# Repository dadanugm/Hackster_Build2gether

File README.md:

# Hackster_Build2gether
Hackster_Build2gether contest repo

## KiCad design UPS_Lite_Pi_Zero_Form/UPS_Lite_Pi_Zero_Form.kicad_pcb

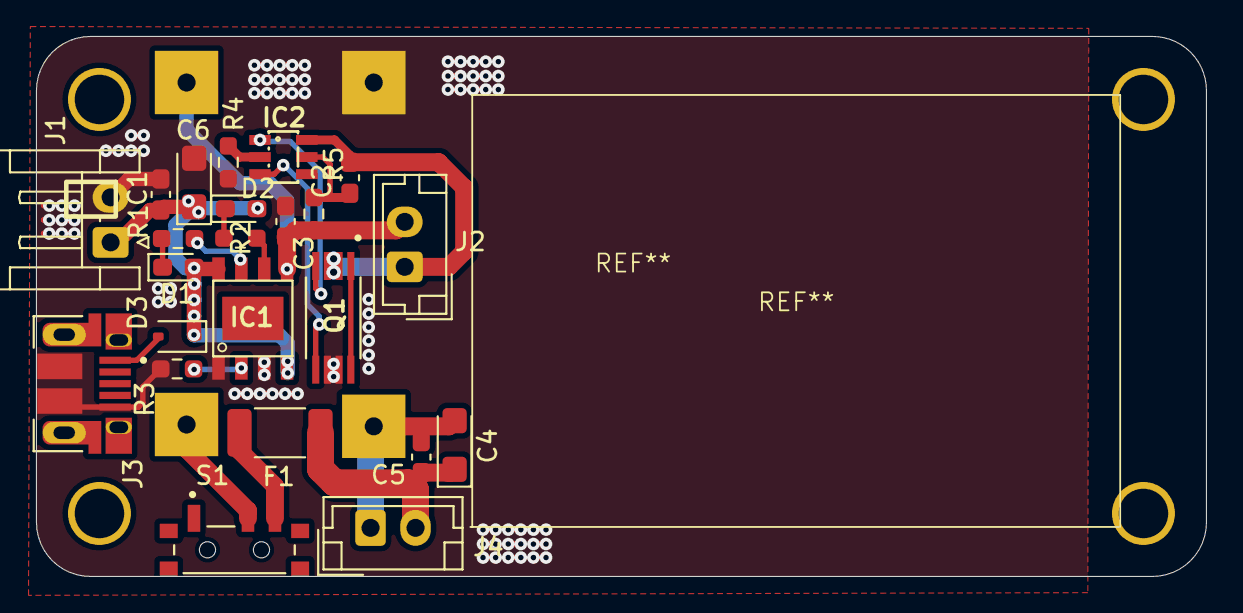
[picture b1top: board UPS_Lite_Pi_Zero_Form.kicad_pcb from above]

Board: 2 copper layers, 65.0 x 30.0 mm, 24 parts (1 on the bottom side), 19 nets.

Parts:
C1, C2: 100nf; C_0603_1608Metric_Pad1.08x0.95mm_HandSolder
C3, C5: 10uF; C_0603_1608Metric_Pad1.08x0.95mm_HandSolder
C4, C6: C_Polarized; CP_EIA-3216-18_Kemet-A
D1, D2: LED; LED_0603_1608Metric_Pad1.05x0.95mm_HandSolder
D3: 1N5819WS; D_SOD-323
F1: Polyfuse_Small; Fuse_2010_5025Metric
IC1: TP4056
IC2: DW01A
J1: Conn_01x02_Male; JST_EH_S2B-EH_1x02_P2.50mm_Horizontal
J2, J4: Conn_01x02_Male; JST_EH_B2B-EH-A_1x02_P2.50mm_Vertical
J3: Micro-USB1
Q1: FS8205A; FS8205
R1, R2, R4: 1K; R_0603_1608Metric_Pad0.98x0.95mm_HandSolder
R3: 1.2K; R_0603_1608Metric_Pad0.98x0.95mm_HandSolder
R5: 100; R_0603_1608Metric_Pad0.98x0.95mm_HandSolder
S1: EG1215AA; SW_Slide_SPST_Side
U*1: Boost_5V_3A

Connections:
/5V_3A: C4.1, C5.1, F1.2, J4.2
/BATT+: C3.1, IC1.5 (BAT), J2.2, R5.2, U*1.1 (IN+)
/BATT-: C2.2, IC2.6 (GND), J2.1, Q1.2, Q1.3
/BATT_SAVE: C2.1, IC2.5 (VCC), R5.1
/BATT_VIN: C1.1, C6.1, D1.2 (A), D2.2 (A), D3.1 (K), IC1.4 (VCC), IC1.8 (CE), J1.1
/CS: IC2.2 (CS), R4.1
/OC: IC2.3 (OC), Q1.5
/OD: IC2.1 (OD), Q1.4
GND: C1.2, C3.2, C6.2, IC1.1 (TEMP), IC1.3 (GND), J1.2, J3.5 (GND), J3.6 (SHIELD), J3.7 (SHIELD), J3.8 (SHIELD), J3.9 (SHIELD), J3.10 (SHIELD), J3.11 (SHIELD), J3.S1 (SHIELD), J3.S2 (SHIELD), Q1.6, Q1.7, R3.1, R4.2, U*1.2 (IN-)
unnamed: D1.1 (K), R1.2
unnamed: D2.1 (K), R2.2
unnamed: D3.2 (A), J3.1 (VCC)
unnamed: F1.1, S1.3
unnamed: IC1.7 (CHRG), R1.1
unnamed: IC1.2 (PROG), R3.2
unnamed: IC1.6 (STDBY), R2.1
unnamed: C4.2, C5.2, J4.1, U*1.4 (OUT-)
unnamed: Q1.1, Q1.8
unnamed: S1.2, U*1.3 (OUT+)

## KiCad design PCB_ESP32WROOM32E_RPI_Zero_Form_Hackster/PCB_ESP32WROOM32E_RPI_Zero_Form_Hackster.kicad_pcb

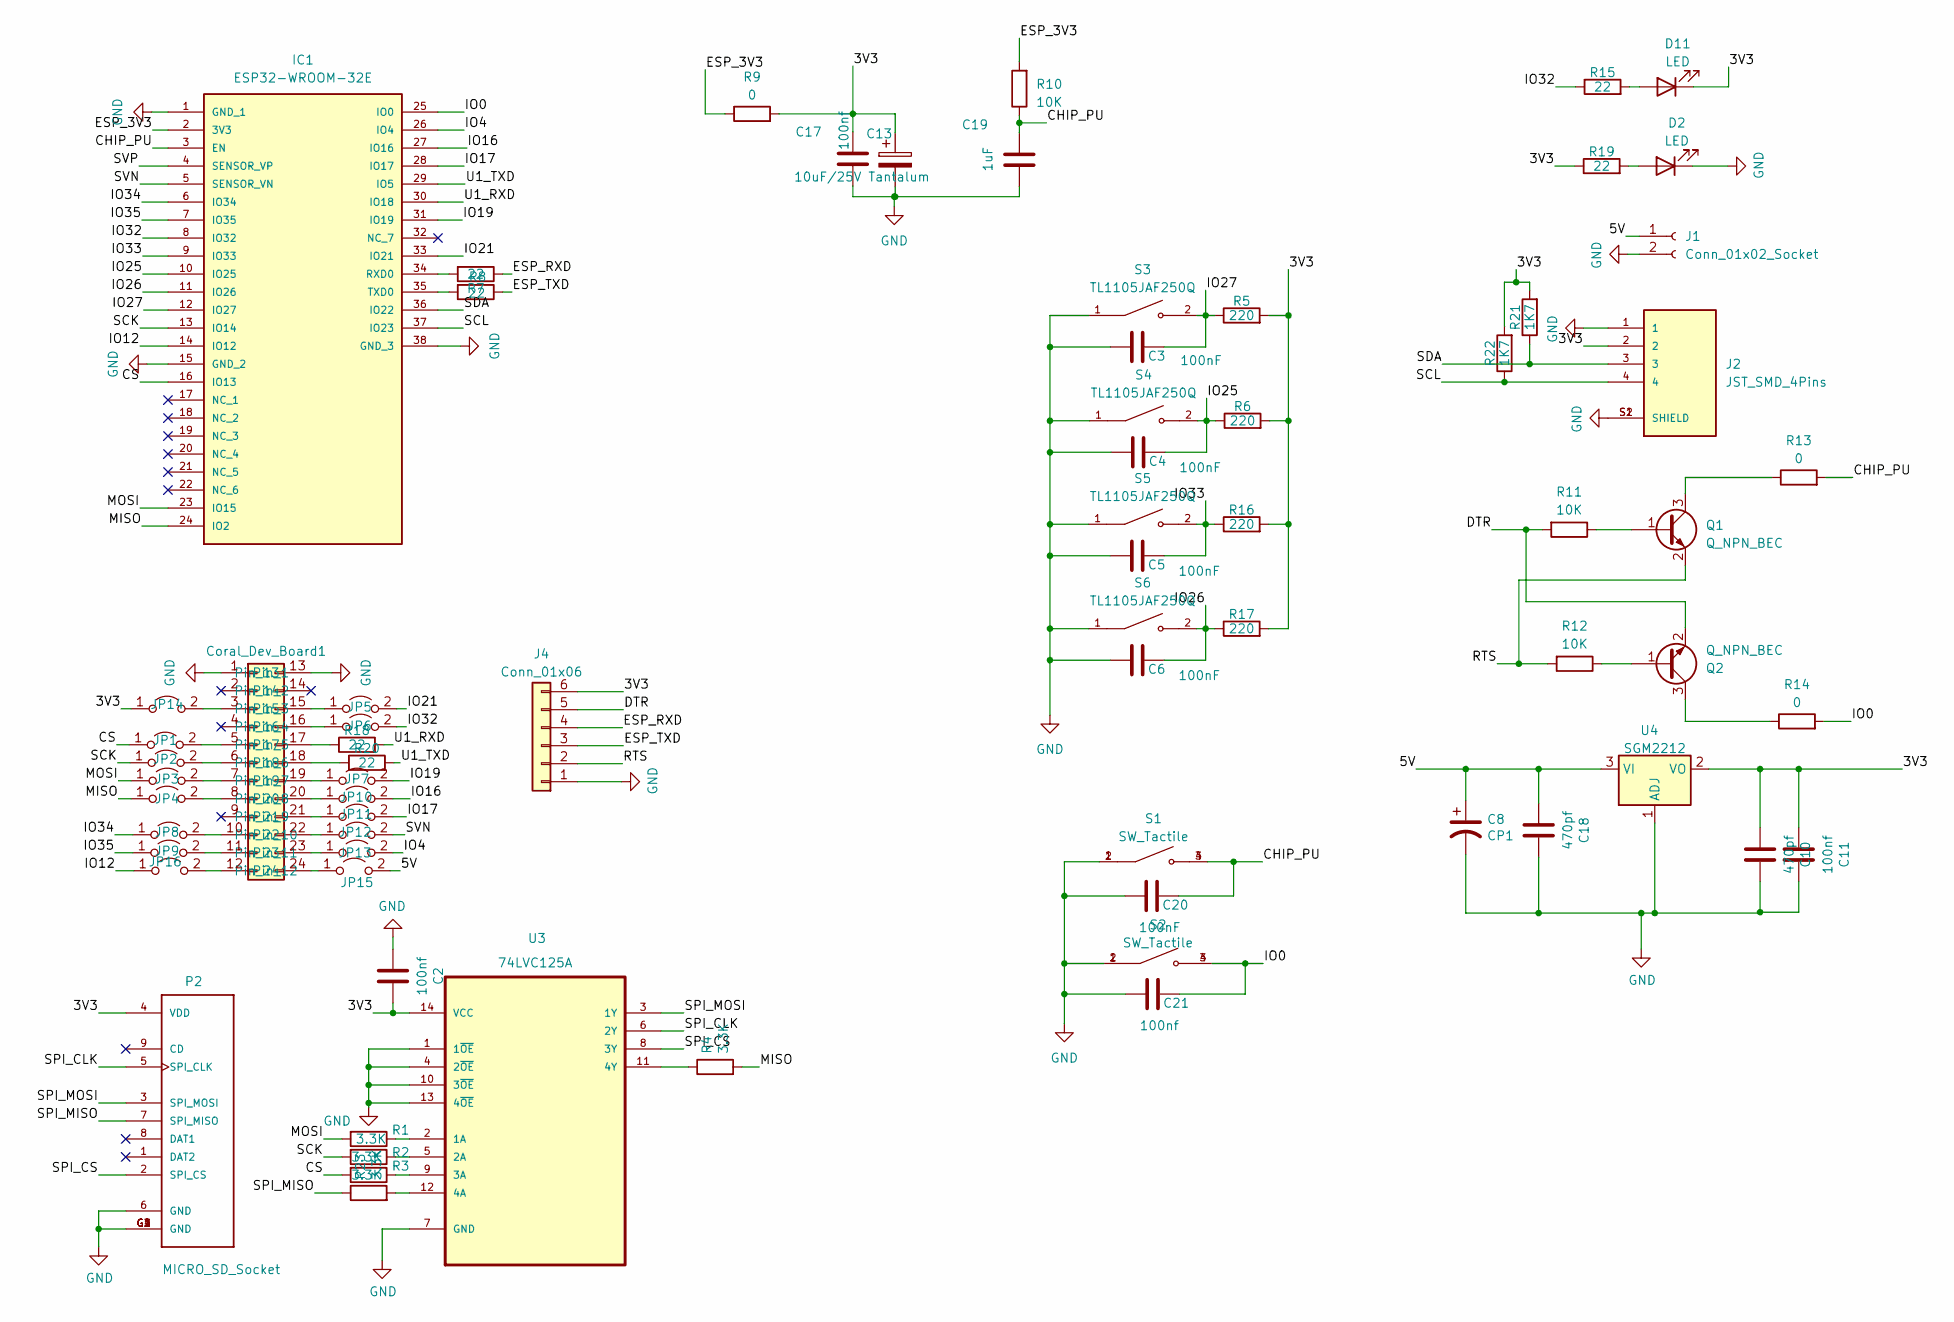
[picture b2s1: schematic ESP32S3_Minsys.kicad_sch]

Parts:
C2, C11, C17, C21: 100nf; C_0603_1608Metric_Pad1.08x0.95mm_HandSolder
C3, C4, C5, C6, C20: 100nF; C_0603_1608Metric_Pad1.08x0.95mm_HandSolder
C8: CP1; CP_EIA-3216-18_Kemet-A
C10, C18: 470pf; C_0603_1608Metric_Pad1.08x0.95mm_HandSolder
C13: 10uF/25V Tantalum; CP_EIA-3216-18_Kemet-A_Pad1.58x1.35mm_HandSolder
C19: 1uF; C_0603_1608Metric_Pad1.08x0.95mm_HandSolder
Coral_Dev_Board1: Coral_dev_micro_board
D2, D11: LED; LED_0603_1608Metric_Pad1.05x0.95mm_HandSolder
IC1: ESP32-WROOM-32E; ESP32_WROOM32E
J1: Conn_01x02_Socket; JST_EH_B2B-EH-A_1x02_P2.50mm_Vertical
J2: JST_SMD_4Pins; JST_4P_1mm; PARTREV N/A
J4: Conn_01x06; JST_EH_S6B-EH_1x06_P2.50mm_Horizontal
JP1, JP2, JP3, JP4, JP5, JP6, JP7, JP8, JP9, JP10, JP11, JP12, JP13, JP14, JP15, JP16: Jumper_2_Open; Custom_Jumper
P2: MICRO_SD_Socket; MicroSD_Footprints
Q1, Q2: Q_NPN_BEC; SOT-23
R1, R2, R3, R4, R23: 3.3K; R_0603_1608Metric_Pad0.98x0.95mm_HandSolder
R5, R6, R16, R17: 220; R_0603_1608Metric_Pad0.98x0.95mm_HandSolder
R7, R8, R15, R18, R19, R20: 22; R_0603_1608Metric_Pad0.98x0.95mm_HandSolder
R9, R13, R14: 0; R_0603_1608Metric_Pad0.98x0.95mm_HandSolder
R10, R11, R12: 10K; R_0603_1608Metric_Pad0.98x0.95mm_HandSolder
R21, R22: 1K7; R_0603_1608Metric_Pad0.98x0.95mm_HandSolder
S1, S2: SW_Tactile
S3, S4, S5, S6: TL1105JAF250Q; SW_Tactile_side; PARTREV F
U3: 74LVC125A; MPN 74LVC125APW,112
U4: SGM2212; SOT-223-3_TabPin2

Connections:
/ESP32S3_Minsys/3V3: C2.1, C10.2, C11.2, C13.1, C17.2, D11.1 (K), J2.2, J4.6, JP14.1 (A), P2.4 (VDD), R5.2, R6.2, R9.2, R16.2, R17.2, R19.1, R21.2, R22.2, U3.14 (VCC), U4.2 (VO)
/ESP32S3_Minsys/5V: C8.1, C18.2, J1.1, JP15.2 (B), U4.3 (VI)
/ESP32S3_Minsys/CHIP_PU: C19.2, C20.1, IC1.3 (EN), R10.1, R13.2, S1.3, S1.4
/ESP32S3_Minsys/CS: IC1.16 (IO13), JP1.1 (A), R3.2
/ESP32S3_Minsys/DTR: J4.5, Q2.2 (E), R11.2
/ESP32S3_Minsys/ESP_3V3: IC1.2 (3V3), R9.1, R10.2
/ESP32S3_Minsys/ESP_RXD: J4.4, R7.1
/ESP32S3_Minsys/ESP_TXD: J4.3, R8.1
/ESP32S3_Minsys/IO0: C21.1, IC1.25 (IO0), R14.2, S2.3, S2.4
/ESP32S3_Minsys/IO4: IC1.26 (IO4), JP13.2 (B)
/ESP32S3_Minsys/IO12: IC1.14 (IO12), JP16.1 (A)
/ESP32S3_Minsys/IO16: IC1.27 (IO16), JP10.2 (B)
/ESP32S3_Minsys/IO17: IC1.28 (IO17), JP11.2 (B)
/ESP32S3_Minsys/IO19: IC1.31 (IO19), JP7.2 (B)
/ESP32S3_Minsys/IO21: IC1.33 (IO21), JP5.2 (B)
/ESP32S3_Minsys/IO25: C4.1, IC1.10 (IO25), R6.1, S4.2
/ESP32S3_Minsys/IO26: C6.1, IC1.11 (IO26), R17.1, S6.2
/ESP32S3_Minsys/IO27: C3.1, IC1.12 (IO27), R5.1, S3.2
/ESP32S3_Minsys/IO32: IC1.8 (IO32), JP6.2 (B), R15.1
/ESP32S3_Minsys/IO33: C5.1, IC1.9 (IO33), R16.1, S5.2
/ESP32S3_Minsys/IO34: IC1.6 (IO34), JP8.1 (A)
/ESP32S3_Minsys/IO35: IC1.7 (IO35), JP9.1 (A)
/ESP32S3_Minsys/MISO: IC1.24 (IO2), JP4.1 (A), R4.2
/ESP32S3_Minsys/MOSI: IC1.23 (IO15), JP3.1 (A), R1.2
/ESP32S3_Minsys/RTS: J4.2, Q1.2 (E), R12.2
/ESP32S3_Minsys/SCK: IC1.13 (IO14), JP2.1 (A), R2.2
/ESP32S3_Minsys/SCL: IC1.37 (IO23), J2.4, R22.1
/ESP32S3_Minsys/SDA: IC1.36 (IO22), J2.3, R21.1
/ESP32S3_Minsys/SPI_CLK: P2.5 (SPI_CLK), U3.6 (2Y)
/ESP32S3_Minsys/SPI_CS: P2.2 (SPI_CS), U3.8 (3Y)
/ESP32S3_Minsys/SPI_MISO: P2.7 (SPI_MISO), R23.1
/ESP32S3_Minsys/SPI_MOSI: P2.3 (SPI_MOSI), U3.3 (1Y)
/ESP32S3_Minsys/SVN: IC1.5 (SENSOR_VN), JP12.2 (B)
/ESP32S3_Minsys/SVP: IC1.4 (SENSOR_VP)
/ESP32S3_Minsys/U1_RXD: IC1.30 (IO18), R18.2
/ESP32S3_Minsys/U1_TXD: IC1.29 (IO5), R20.2
GND: C2.2, C3.2, C4.2, C5.2, C6.2, C8.2, C10.1, C11.1, C13.2, C17.1, C18.1, C19.1, C20.2, C21.2, Coral_Dev_Board1.1, Coral_Dev_Board1.13, D2.1 (K), IC1.1 (GND_1), IC1.15 (GND_2), IC1.38 (GND_3), J1.2, J2.1, J2.S1 (SHIELD), J2.S2 (SHIELD), J4.1, P2.6 (GND), P2.G1 (GND), P2.G2 (GND), P2.G3 (GND), P2.G4 (GND), S1.1, S1.2, S2.1, S2.2, S3.1, S4.1, S5.1, S6.1, U3.1 (1~OE), U3.4 (2~OE), U3.7 (GND), U3.10 (3~OE), U3.13 (4~OE), U4.1 (ADJ)
unnamed: Coral_Dev_Board1.3, JP14.2 (B)
unnamed: Coral_Dev_Board1.5, JP1.2 (B)
unnamed: Coral_Dev_Board1.6, JP2.2 (B)
unnamed: Coral_Dev_Board1.7, JP3.2 (B)
unnamed: Coral_Dev_Board1.8, JP4.2 (B)
unnamed: Coral_Dev_Board1.10, JP8.2 (B)
unnamed: Coral_Dev_Board1.11, JP9.2 (B)
unnamed: Coral_Dev_Board1.12, JP16.2 (B)
unnamed: Coral_Dev_Board1.15, JP5.1 (A)
unnamed: Coral_Dev_Board1.16, JP6.1 (A)
unnamed: Coral_Dev_Board1.17, R18.1
unnamed: Coral_Dev_Board1.18, R20.1
unnamed: Coral_Dev_Board1.19, JP7.1 (A)
unnamed: Coral_Dev_Board1.20, JP10.1 (A)
unnamed: Coral_Dev_Board1.21, JP11.1 (A)
unnamed: Coral_Dev_Board1.22, JP12.1 (A)
unnamed: Coral_Dev_Board1.23, JP13.1 (A)
unnamed: Coral_Dev_Board1.24, JP15.1 (A)
unnamed: D2.2 (A), R19.2
unnamed: D11.2 (A), R15.2
unnamed: IC1.34 (RXD0), R7.2
unnamed: IC1.35 (TXD0), R8.2
unnamed: Q1.1 (B), R11.1
unnamed: Q1.3 (C), R13.1
unnamed: Q2.1 (B), R12.1
unnamed: Q2.3 (C), R14.1
unnamed: R1.1, U3.2 (1A)
unnamed: R2.1, U3.5 (2A)
unnamed: R3.1, U3.9 (3A)
unnamed: R23.2, U3.12 (4A)
unnamed: R4.1, U3.11 (4Y)

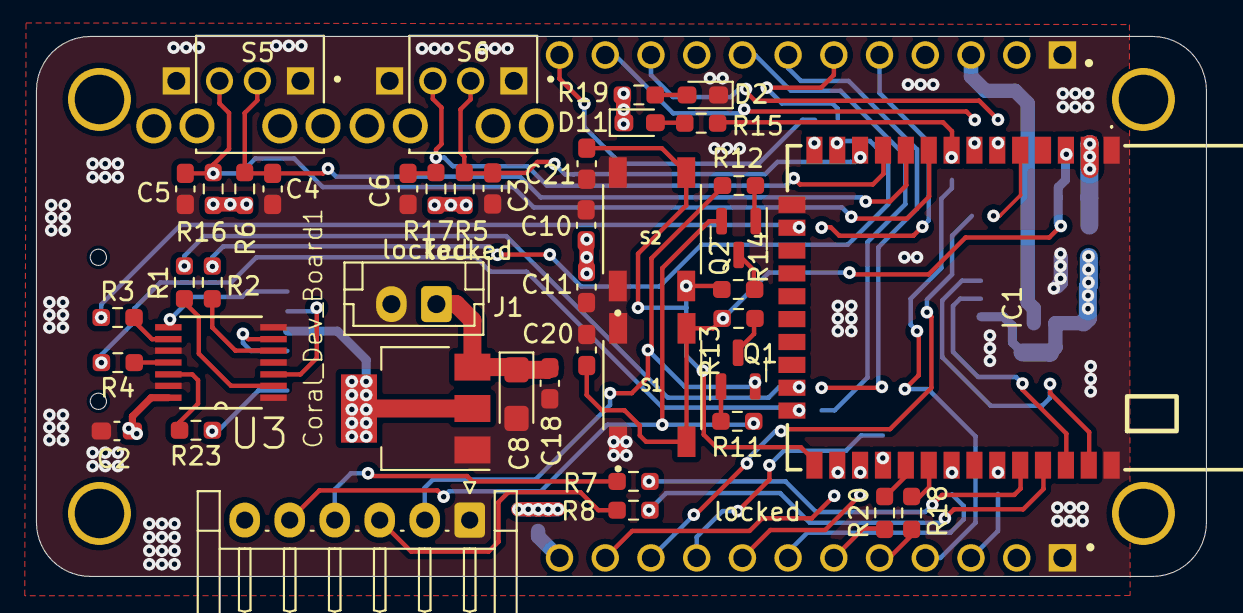
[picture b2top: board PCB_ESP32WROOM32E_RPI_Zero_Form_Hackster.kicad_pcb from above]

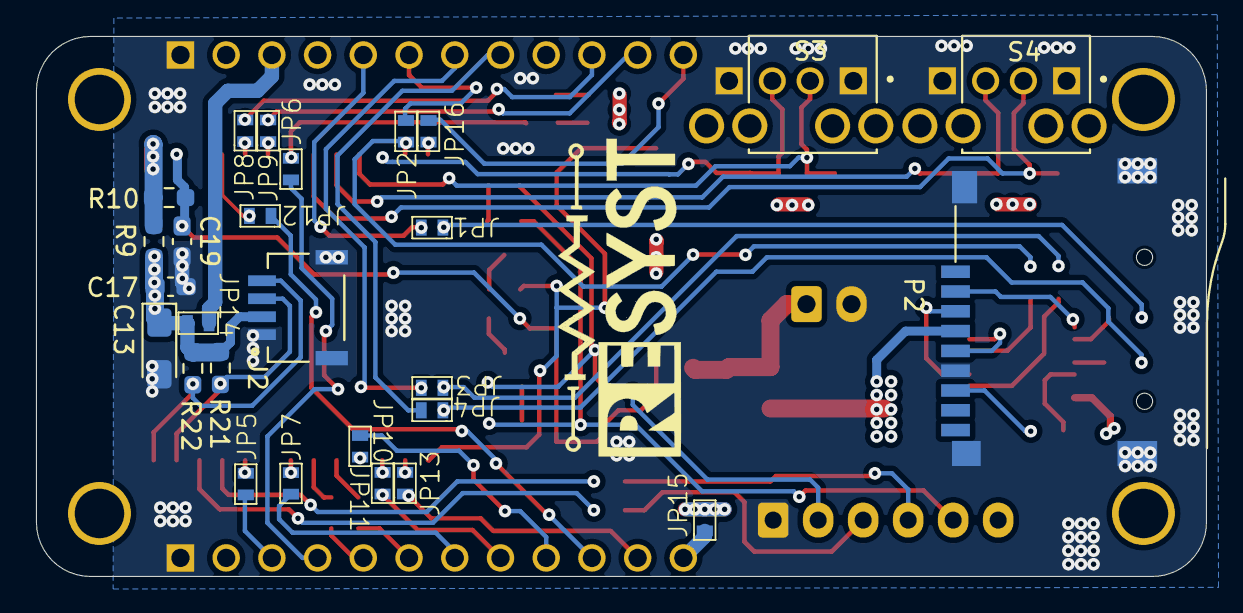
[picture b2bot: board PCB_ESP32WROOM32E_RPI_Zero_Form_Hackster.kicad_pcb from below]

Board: 4 copper layers, 65.0 x 30.0 mm, 71 parts (27 on the bottom side), 67 nets.

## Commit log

2023-09-09 Update training
2023-11-24 PCB Upload
2023-11-26 Board pictures
